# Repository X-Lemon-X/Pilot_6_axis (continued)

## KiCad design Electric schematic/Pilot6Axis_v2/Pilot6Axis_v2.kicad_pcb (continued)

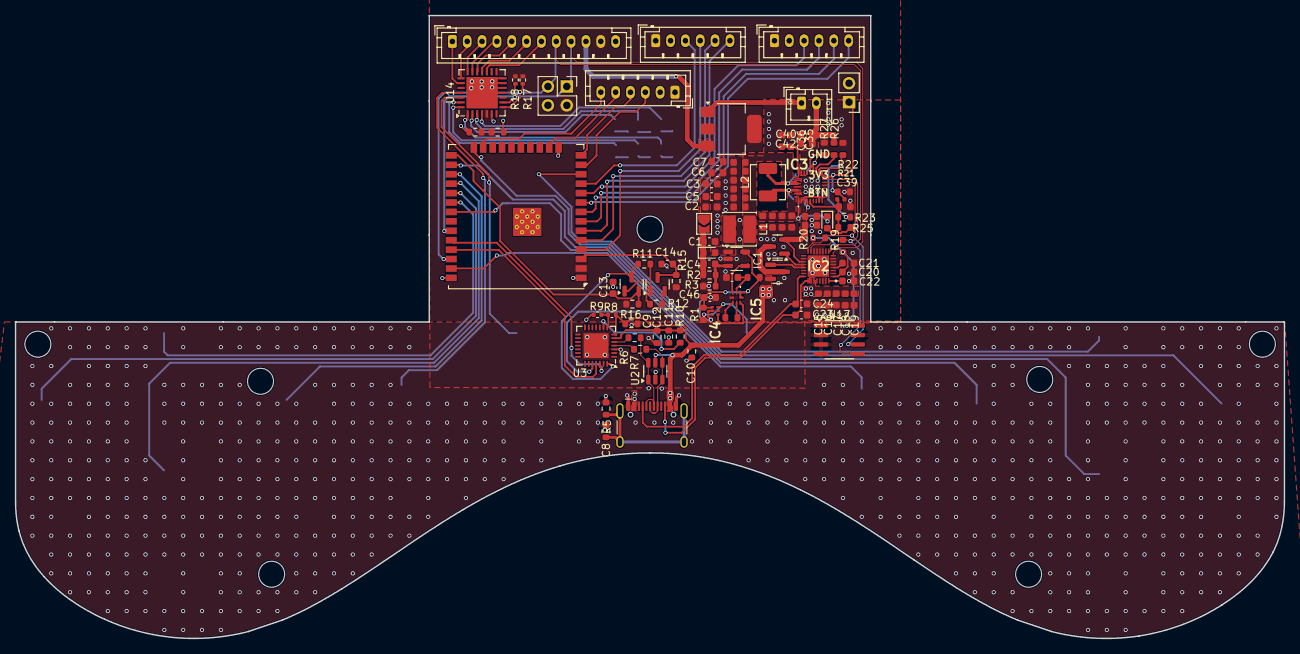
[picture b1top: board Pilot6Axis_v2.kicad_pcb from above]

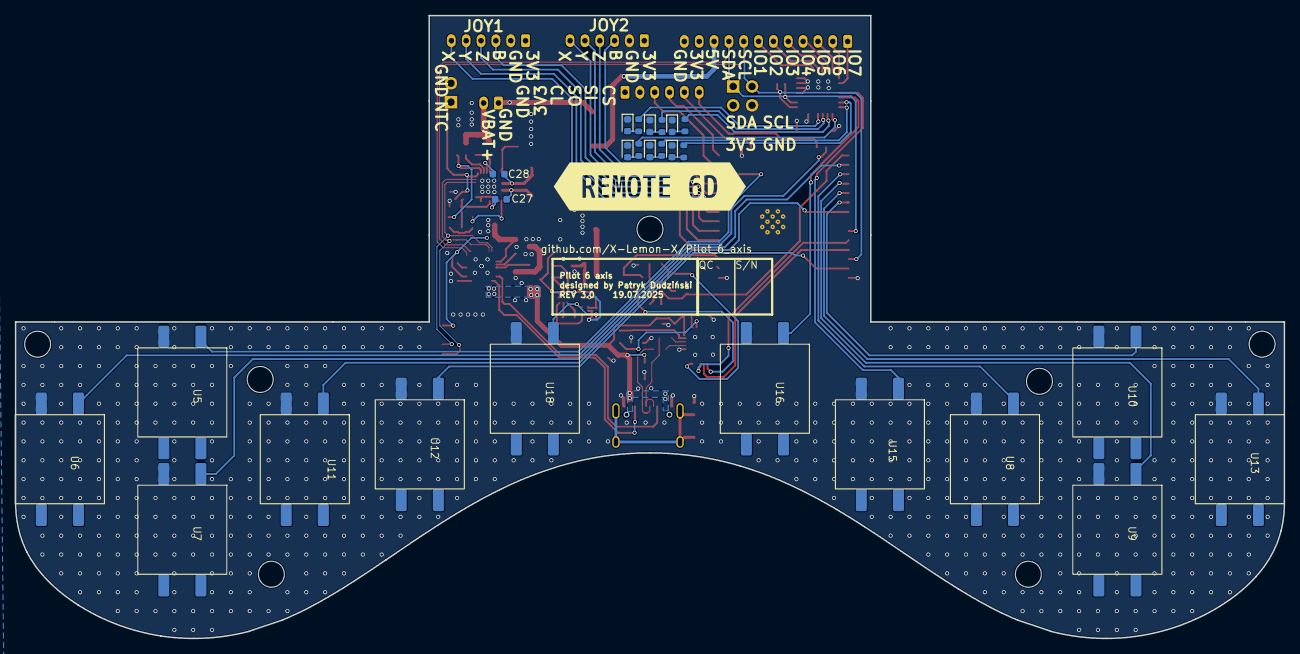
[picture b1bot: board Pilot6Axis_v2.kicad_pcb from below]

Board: 2 copper layers, 171.0 x 83.9 mm, 126 parts (27 on the bottom side), 99 nets.

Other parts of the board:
kibuzzard-6828A41A: G***; kibuzzard-6828A41A

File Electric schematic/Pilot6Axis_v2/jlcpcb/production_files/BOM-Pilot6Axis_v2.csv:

Comment,Designator,Footprint,LCSC,Quantity
10uH,L1,L_Cenker_CKCS4018,C1035,1
40.5k,R2,R_0603_1608Metric,C12447,1
100n,"C10,C11,C17,C18,C19,C22,C25,C26,C3,C34,C43,C45,C46,C7",R_0603_1608Metric,C14663,14
1k,R10,R_0603_1608Metric,C14676,1
1nF,"C13,C14,C35,C36,C47,C5,C6",C_0603_1608Metric,C1588,7
220pF,"C23,C24,C4",C_0603_1608Metric,C1603,3
47nF,"C27,C28",C_0603,C1622,2
4.7uF,"C1,C16,C39",C_0603_1608Metric,C19666,3
10u,"C12,C44,C9",R_0603_1608Metric,C19702,3
S9014,"Q1,Q2",Q_SOT-23,C20069130,2
AO3400A,"Q3,Q4",Q_SOT-23,C20917,2
1kΩ,"R13,R14,R25,R28,R30,R31,R32",R_0603,C21190,7
100Ω,R26,R_0603,C22775,1
Red,"D2,D3,D4,D5,D6,D7,D8",D_0603,C2286,7
30kΩ,R22,R_0603,C22984,1
330Ω,R4,R_0603,C23138,1
4.7kΩ,"R19,R20",R_0603,C23162,2
22Ω,R29,R_0603,C23345,1
100kΩ,"R1,R24",R_0603,C25803,2
5.1kΩ,R21,R_0402,C25905,1
13.3k,"R11,R12,R15,R16,R17,R18,R3,R8,R9",R_0603_1608Metric,C25952,9
USB_C_Receptacle_USB2.0_16P,J3,USB_C_Receptacle_HCTL_HC-TYPE-C-16P-01A,C2765186,1
MBR0520,D1,D_0603_1608Metric,C2858712,1
LM27313XMFX_NOPB,IC1,SOT-23-5,C341750,1
3kΩ,R27,R_0603,C4211,1
33k,R5,R_0603_1608Metric,C4216,1
USBLC6-2SC6,U2,SOT-23-6,C5180249,1
10nF,C8,R_0603_1608Metric,C57112,1
AMS1117-3.3,U1,SOT-223-3_TabPin2,C6186,1
22R,"R6,R7",R_0603_1608Metric,C71618,2
10uF,"C15,C2,C20,C21,C29,C30,C31,C32,C33,C37,C38,C40,C41,C42",C_0603,C96446,14
CP2102N-Axx-xQFN28,U3,QFN-28-1EP_5x5mm_P0.5mm_EP3.35x3.35mm,C964632,1
127k,R23,R_0603_1608Metric,,1
Conn_01x06,J9,JST_PH_B6B-PH-K_1x06_P2.00mm_Vertical,,1
TPS25751SRSMR,IC2,QFN40P400X400X100-33N-D,,1
SolderJumper_2_Bridged,JP1,SolderJumper-2_P1.3mm_Open_TrianglePad1.0x1.5mm,,1
Conn_01x12,J8,JST_PH_B12B-PH-K_1x12_P2.00mm_Vertical,,1
Conn_01x06,J4,JST_PH_B6B-PH-K_1x06_P2.00mm_Vertical,,1
MCP23017_ML,U14,QFN-28-1EP_6x6mm_P0.65mm_EP4.25x4.25mm,,1
10k,TH1,PinHeader_1x02_P2.54mm_Vertical,,1
TPS3422EGDRYR,IC4,DRY_R-PUSON-N6_,,1
SN74LVC1G74RSE2,IC5,SN74LVC1G74RSE2,,1
BQ25792RQMR,IC3,BQ25792RQMR,,1
1u,L2,L_APV_APH0420,,1
ESP32-WROOM-32U,U4,ESP32-WROOM-32U,,1
Battery input,J1,JST_PH_B2B-PH-K_1x02_P2.00mm_Vertical,,1
Conn_01x06,J10,JST_PH_B6B-PH-K_1x06_P2.00mm_Vertical,,1
Oled,J6,PinSocket_2x02_P2.54mm_Vertical,,1
~,U12,ts-1212f,,1
~,U7,ts-1212f,,1
~,U9,ts-1212f,,1
Power switch,U18,ts-1212f,,1
~,U6,ts-1212f,,1
~,U10,ts-1212f,,1
~,U11,ts-1212f,,1
~,U8,ts-1212f,,1
~,U15,ts-1212f,,1
~,U13,ts-1212f,,1
~,U16,ts-1212f,,1
~,U5,ts-1212f,,1
CAT24C512WI-GT3,U17,SOIC-8_3.9x4.9mm_P1.27mm,,1

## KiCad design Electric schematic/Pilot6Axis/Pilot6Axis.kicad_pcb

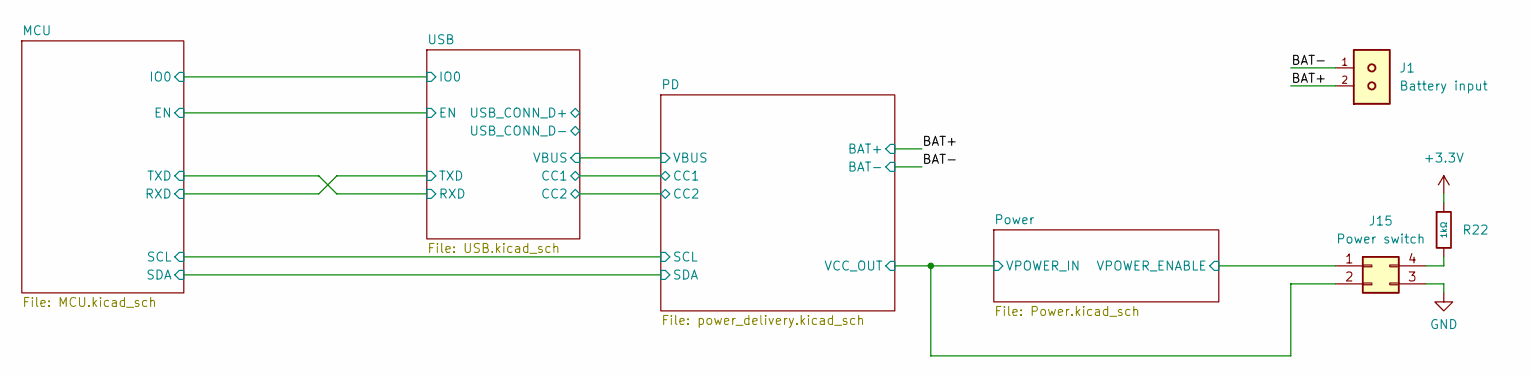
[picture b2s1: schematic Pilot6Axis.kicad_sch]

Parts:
J1: Battery input; Molex_KK-254_AE-6410-02A_1x02_P2.54mm_Vertical
J15: Power switch; Molex_KK-254_AE-6410-04A_1x04_P2.54mm_Vertical
R22: 1kΩ; R_0603; Overload Voltage (Max) 75V; Tolerance ±1%; Part 0603WAF1001T5E; LCSC C21190

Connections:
+3.3V: R22.1; also elsewhere on the board
/BAT+: J1.2; also elsewhere on the board
/PD/VCC_OUT: J15.2; also elsewhere on the board
/Power/VPOWER_ENABLE: J15.1; also elsewhere on the board
GND: J1.1, J15.3; also elsewhere on the board
unnamed: J15.4, R22.2

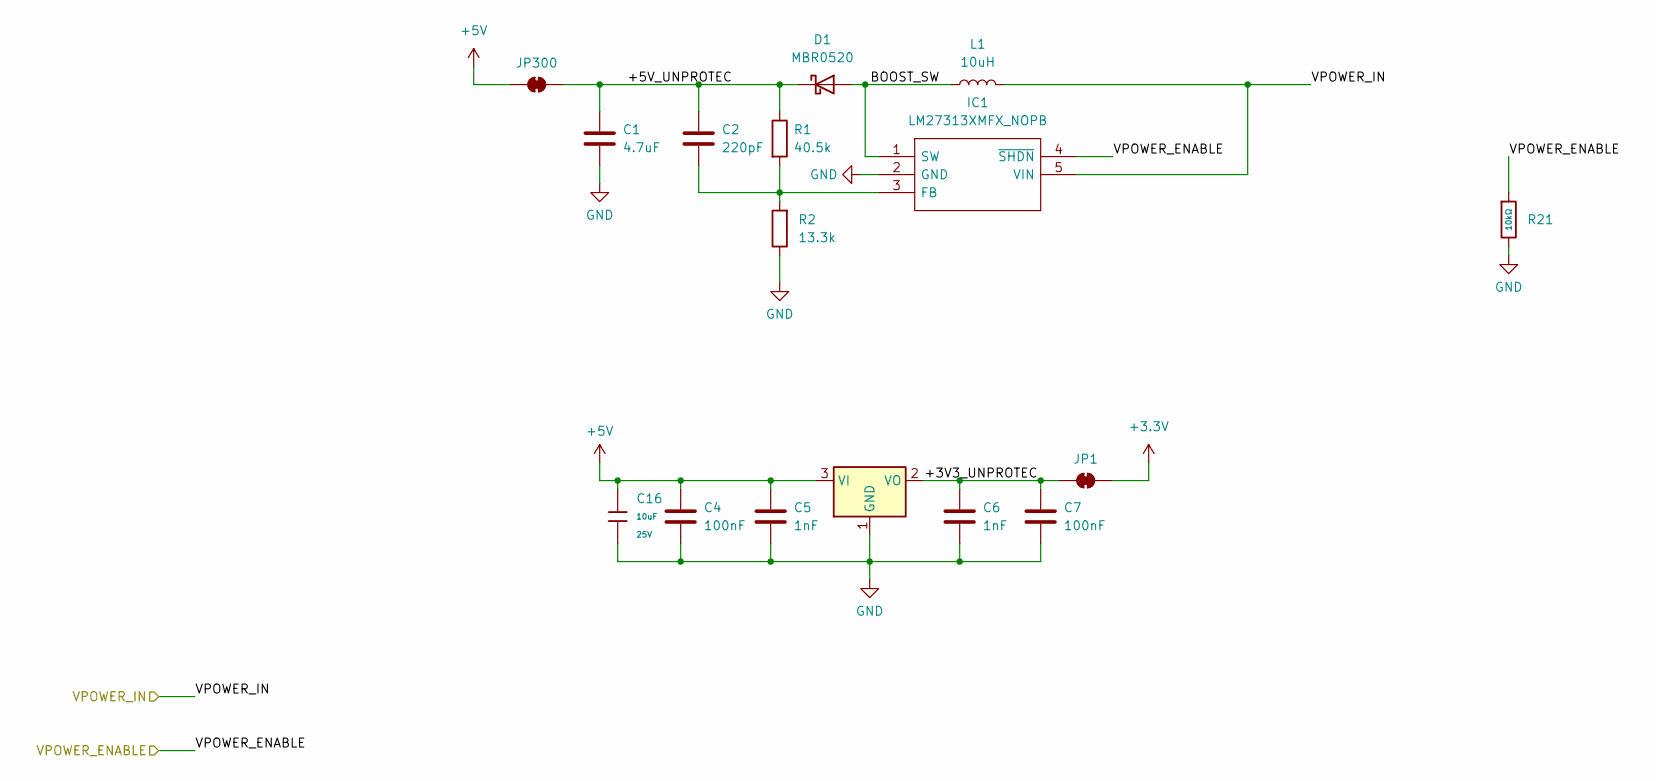
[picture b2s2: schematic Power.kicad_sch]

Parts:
C1: 4.7uF; C_0603_1608Metric; LCSC C19666
C2: 220pF; C_0603_1608Metric; LCSC C1603
C4, C7: 100nF; C_0603_1608Metric; LCSC C14663
C5, C6: 1nF; C_0603_1608Metric; LCSC C1588
C16: 10uF; C_0603; Voltage Rated 25V; Tolerance ±20%; Part CL10A106MA8NRNC; LCSC C96446
D1: MBR0520; D_0603_1608Metric; LCSC C2858712
IC1: LM27313XMFX_NOPB; SOT-23-5; Manufacturer_Part_Number LM27313XMFX/NOPB; Mouser Part Number 926-LM27313XMFX/NOPB
JP1, JP300: SolderJumper_2_Bridged; SolderJumper-2_P1.3mm_Open_TrianglePad1.0x1.5mm
L1: 10uH; L_Cenker_CKCS4018; LCSC C1035
R1: 40.5k; R_0603_1608Metric; LCSC C12447
R2: 13.3k; R_0603_1608Metric; LCSC C25952
R21: 10kΩ; R_0603; Overload Voltage (Max) 75V; Tolerance ±1%; Part 0603WAF1002T5E; LCSC C25804
U1: AMS1117-3.3; SOT-223-3_TabPin2; LCSC C6186

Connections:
+3.3V: JP1.2 (B); also elsewhere on the board
+5V: C4.1, C5.1, C16.1, JP300.1 (A), U1.3 (VI); also elsewhere on the board
/PD/VCC_OUT: IC1.5 (VIN), L1.2; also elsewhere on the board
/Power/+3V3_UNPROTEC: C6.1, C7.1, JP1.1 (A), U1.2 (VO)
/Power/+5V_UNPROTEC: C1.1, C2.2, D1.1 (K), JP300.2 (B), R1.1
/Power/BOOST_SW: D1.2 (A), IC1.1 (SW), L1.1
/Power/VPOWER_ENABLE: IC1.4 (~SHDN), R21.1; also elsewhere on the board
GND: C1.2, C4.2, C5.2, C6.2, C7.2, C16.2, IC1.2 (GND), R2.1, R21.2, U1.1 (GND); also elsewhere on the board
unnamed: C2.1, IC1.3 (FB), R1.2, R2.2

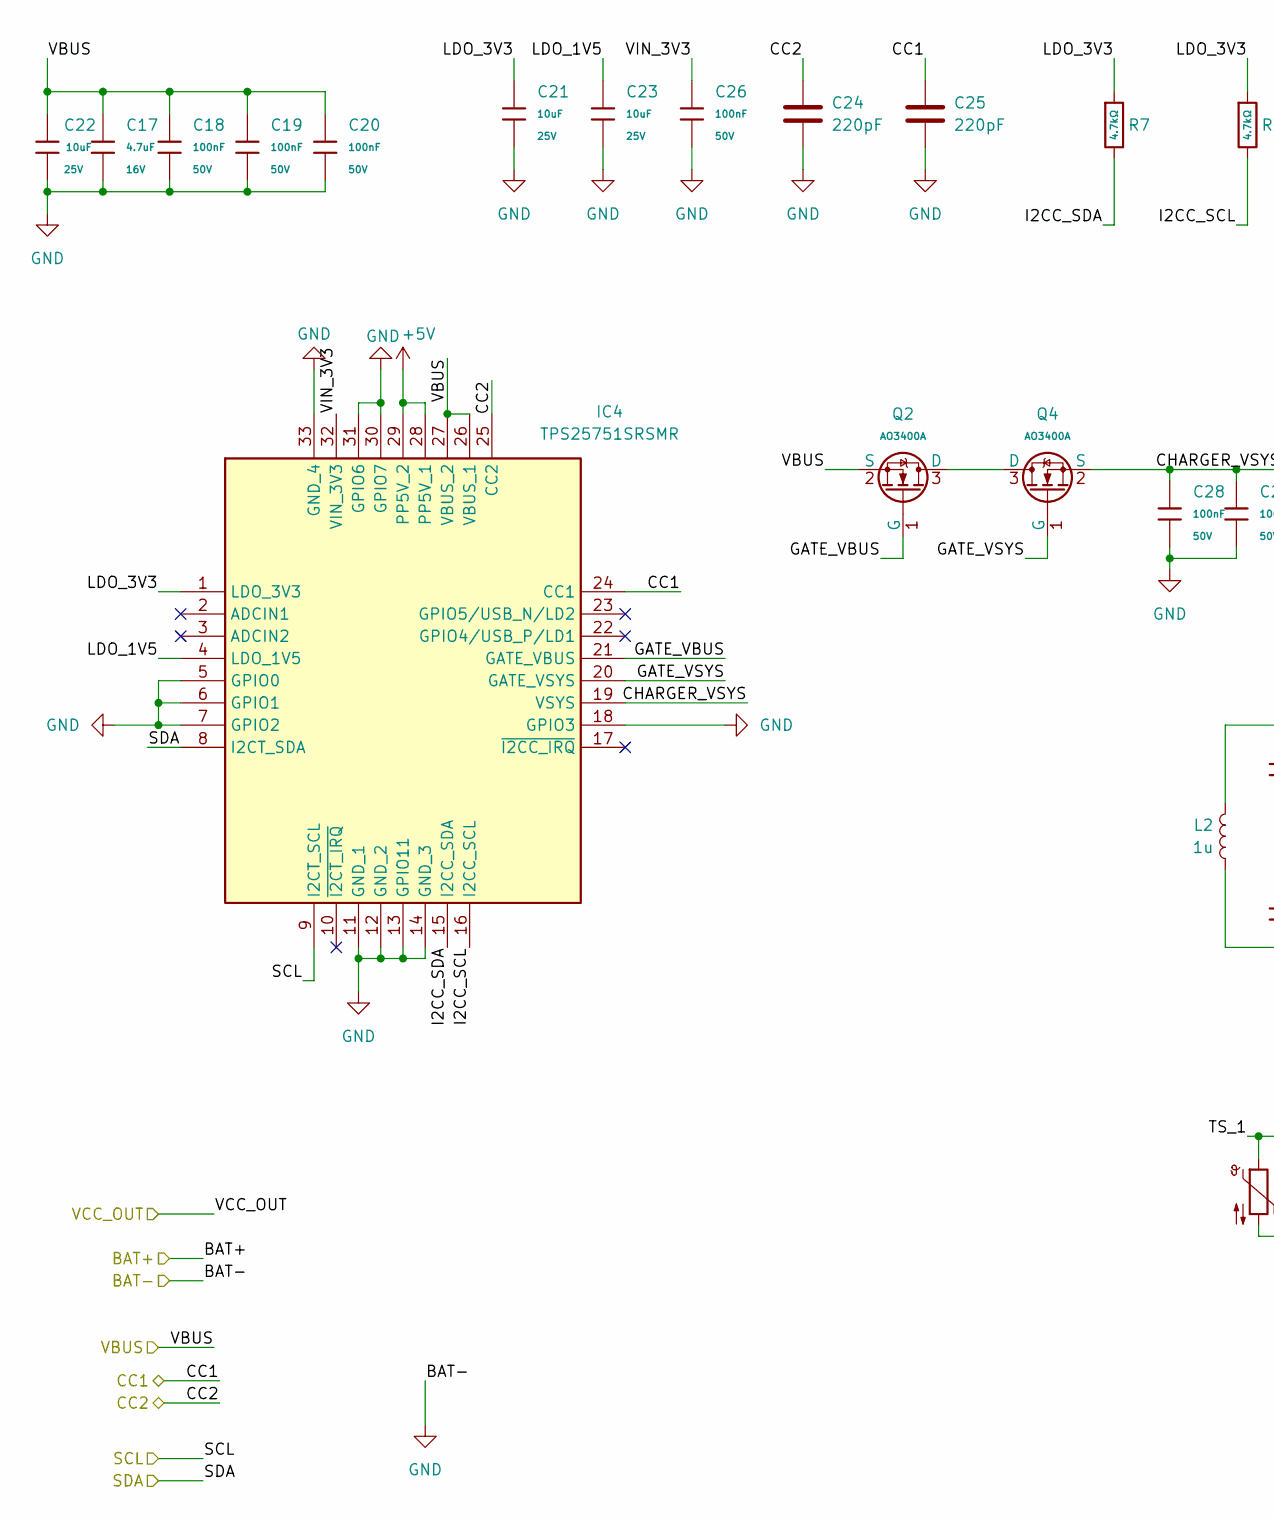
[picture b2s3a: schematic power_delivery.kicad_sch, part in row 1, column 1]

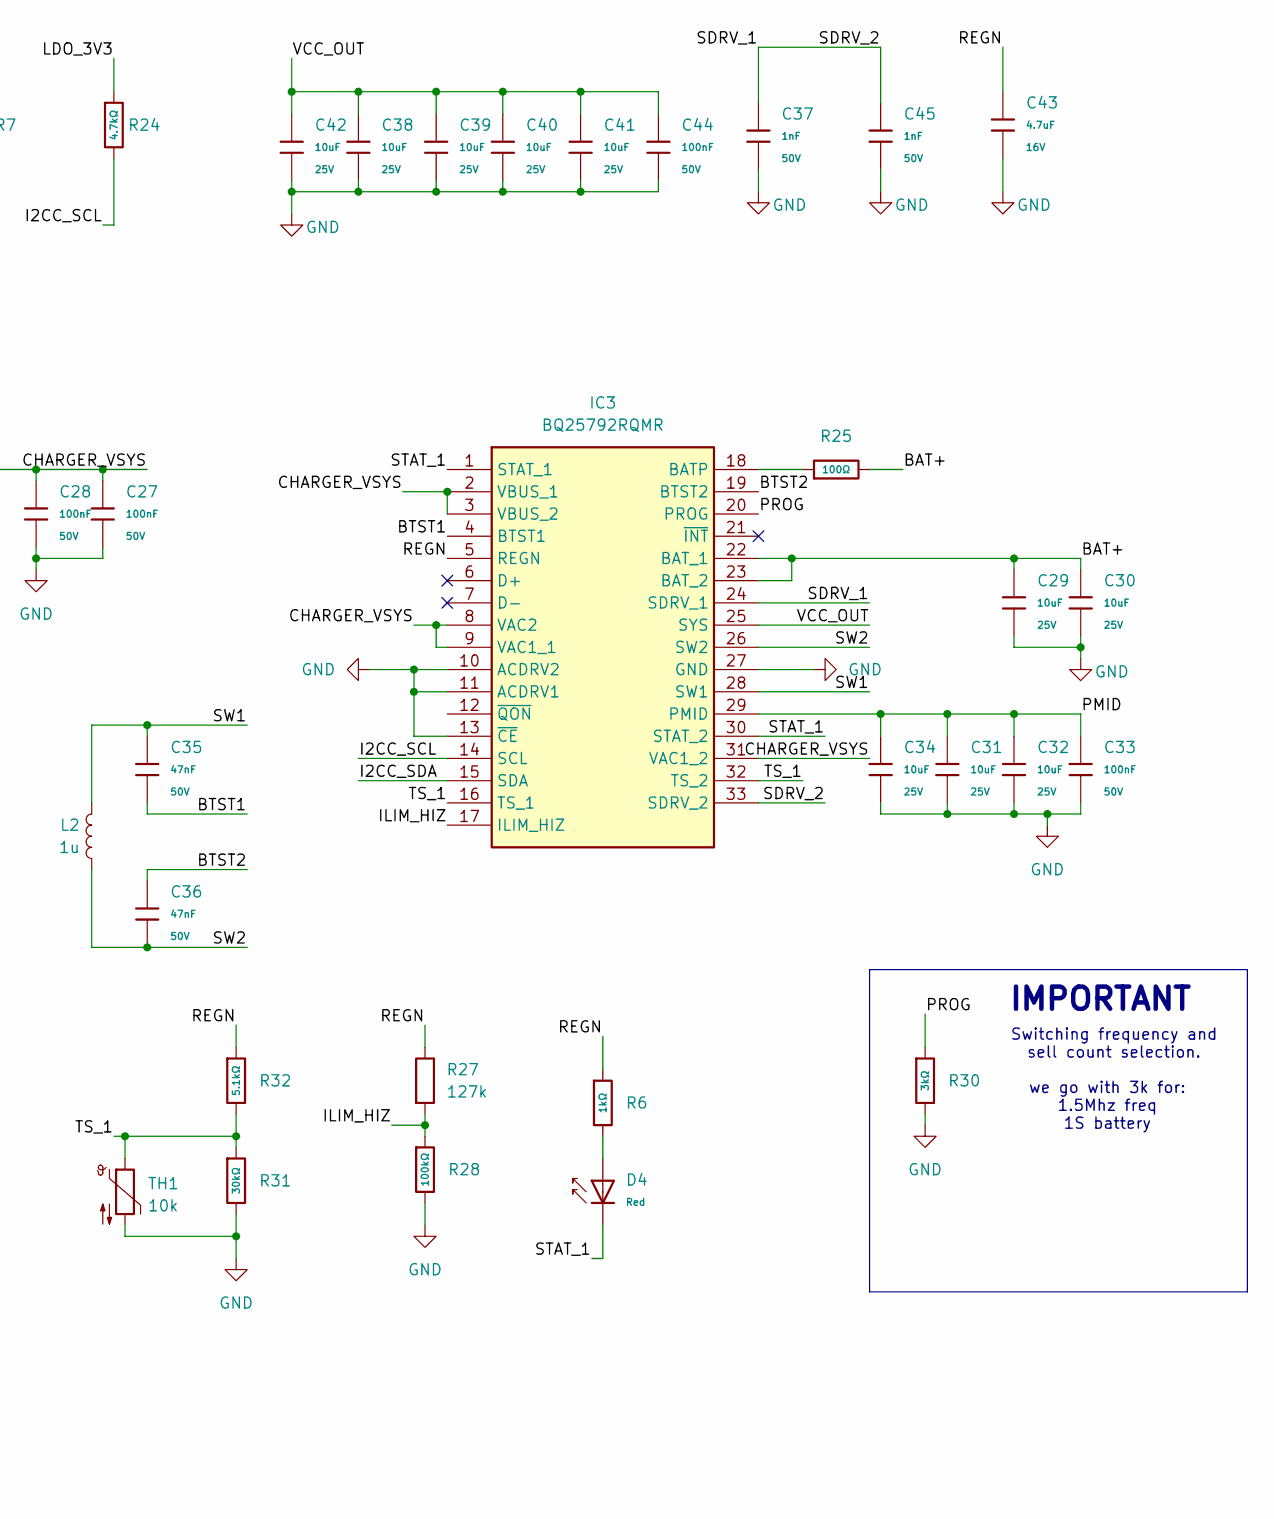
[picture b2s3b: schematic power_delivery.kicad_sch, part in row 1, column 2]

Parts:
C17, C43: 4.7uF; C_0603; Voltage Rated 16V; Tolerance ±10%; Part CL10A475KO8NNNC; LCSC C19666
C18, C19, C20, C26, C27, C28, C33, C44: 100nF; C_0603; Voltage Rated 50V; Tolerance ±10%; Part CC0603KRX7R9BB104; LCSC C14663
C21, C22, C23, C29, C30, C31, C32, C34, C38, C39, C40, C41, C42: 10uF; C_0603; Voltage Rated 25V; Tolerance ±20%; Part CL10A106MA8NRNC; LCSC C96446
C24, C25: 220pF; C_0603_1608Metric; LCSC C1603
C35, C36: 47nF; C_0603; Voltage Rated 50V; Tolerance ±10%; Part CL10B473KB8NNNC; LCSC C1622
C37, C45: 1nF; C_0603; Voltage Rated 50V; Tolerance ±10%; Part CL10B102KB8NNNC; LCSC C1588
D4: Red; D_0603; Part KT-0603R; LCSC C2286
IC3: BQ25792RQMR; Manufacturer_Part_Number BQ25792RQMR; Mouser Part Number 595-BQ25792RQMR
IC4: TPS25751SRSMR; QFN40P400X400X100-33N-D; Manufacturer_Part_Number TPS25751SRSMR; Mouser Part Number 595-TPS25751SRSMR
L2: 1u; L_APV_APH0420
Q2, Q4: AO3400A; Q_SOT-23; Part AO3400A; LCSC C20917
R6: 1kΩ; R_0603; Overload Voltage (Max) 75V; Tolerance ±1%; Part 0603WAF1001T5E; LCSC C21190
R7, R24: 4.7kΩ; R_0603; Overload Voltage (Max) 75V; Tolerance ±1%; Part 0603WAF4701T5E; LCSC C23162
R25: 100Ω; R_0603; Overload Voltage (Max) 75V; Tolerance ±1%; Part 0603WAF1000T5E; LCSC C22775
R27: 127k; R_0603_1608Metric
R28: 100kΩ; R_0603; Overload Voltage (Max) 75V; Tolerance ±1%; Part 0603WAF1003T5E; LCSC C25803
R30: 3kΩ; R_0603; Overload Voltage (Max) 75V; Tolerance ±1%; Part 0603WAF3001T5E; LCSC C4211
R31: 30kΩ; R_0603; Overload Voltage (Max) 75V; Tolerance ±1%; Part 0603WAF3002T5E; LCSC C22984
R32: 5.1kΩ; R_0402; Overload Voltage (Max) 50V; Tolerance ±1%; Part 0402WGF5101TCE; LCSC C25905
TH1: 10k; PinHeader_1x02_P2.54mm_Vertical

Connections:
+5V: IC4.28 (PP5V_1), IC4.29 (PP5V_2); also elsewhere on the board
/BAT+: C29.1, C30.1, IC3.22 (BAT_1), IC3.23 (BAT_2), R25.2; also elsewhere on the board
/MCU/SCL: IC4.9 (I2CT_SCL); also elsewhere on the board
/MCU/SDA: IC4.8 (I2CT_SDA); also elsewhere on the board
/PD/BTST1: C35.2, IC3.4 (BTST1)
/PD/BTST2: C36.1, IC3.19 (BTST2)
/PD/CC1: C25.2, IC4.24 (CC1); also elsewhere on the board
/PD/CC2: C24.2, IC4.25 (CC2); also elsewhere on the board
/PD/CHARGER_VSYS: C27.1, C28.1, IC3.2 (VBUS_1), IC3.3 (VBUS_2), IC3.8 (VAC2), IC3.9 (VAC1_1), IC3.31 (VAC1_2), IC4.19 (VSYS), Q4.2 (S)
/PD/GATE_VBUS: IC4.21 (GATE_VBUS), Q2.1 (G)
/PD/GATE_VSYS: IC4.20 (GATE_VSYS), Q4.1 (G)
/PD/I2CC_SCL: IC3.14 (SCL), IC4.16 (I2CC_SCL), R24.2
/PD/I2CC_SDA: IC3.15 (SDA), IC4.15 (I2CC_SDA), R7.2
/PD/ILIM_HIZ: IC3.17 (ILIM_HIZ), R27.2, R28.1
/PD/LDO_1V5: C23.1, IC4.4 (LDO_1V5)
/PD/LDO_3V3: C21.1, IC4.1 (LDO_3V3), R7.1, R24.1
/PD/PMID: C31.1, C32.1, C33.1, C34.1, IC3.29 (PMID)
/PD/PROG: IC3.20 (PROG), R30.1
/PD/REGN: C43.1, IC3.5 (REGN), R6.1, R27.1, R32.1
/PD/SDRV_1: C37.1, C45.1, IC3.24 (SDRV_1), IC3.33 (SDRV_2)
/PD/STAT_1: D4.1, IC3.1 (STAT_1), IC3.30 (STAT_2)
/PD/SW1: C35.1, IC3.28 (SW1), L2.1
/PD/SW2: C36.2, IC3.26 (SW2), L2.2
/PD/TS_1: IC3.16 (TS_1), IC3.32 (TS_2), R31.1, R32.2, TH1.1
/PD/VBUS: C17.1, C18.1, C19.1, C20.1, C22.1, IC4.26 (VBUS_1), IC4.27 (VBUS_2), Q2.2 (S); also elsewhere on the board
/PD/VCC_OUT: C38.1, C39.1, C40.1, C41.1, C42.1, C44.1, IC3.25 (SYS); also elsewhere on the board
/PD/VIN_3V3: C26.1, IC4.32 (VIN_3V3)
GND: C17.2, C18.2, C19.2, C20.2, C21.2, C22.2, C23.2, C24.1, C25.1, C26.2, C27.2, C28.2, C29.2, C30.2, C31.2, C32.2, C33.2, C34.2, C37.2, C38.2, C39.2, C40.2, C41.2, C42.2, C43.2, C44.2, C45.2, IC3.10 (ACDRV2), IC3.11 (ACDRV1), IC3.13 (~CE), IC3.27 (GND), IC4.5 (GPIO0), IC4.6 (GPIO1), IC4.7 (GPIO2), IC4.11 (GND_1), IC4.12 (GND_2), IC4.13 (GPIO11), IC4.14 (GND_3), IC4.18 (GPIO3), IC4.30 (GPIO7), IC4.31 (GPIO6), IC4.33 (GND_4), R28.2, R30.2, R31.2, TH1.2; also elsewhere on the board
unnamed: D4.2, R6.2
unnamed: IC3.18 (BATP), R25.1
unnamed: Q2.3 (D), Q4.3 (D)

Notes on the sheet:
Switching frequency and sell count selection.
we go with 3k for: 1.5Mhz freq 1S battery
IMPORTANT

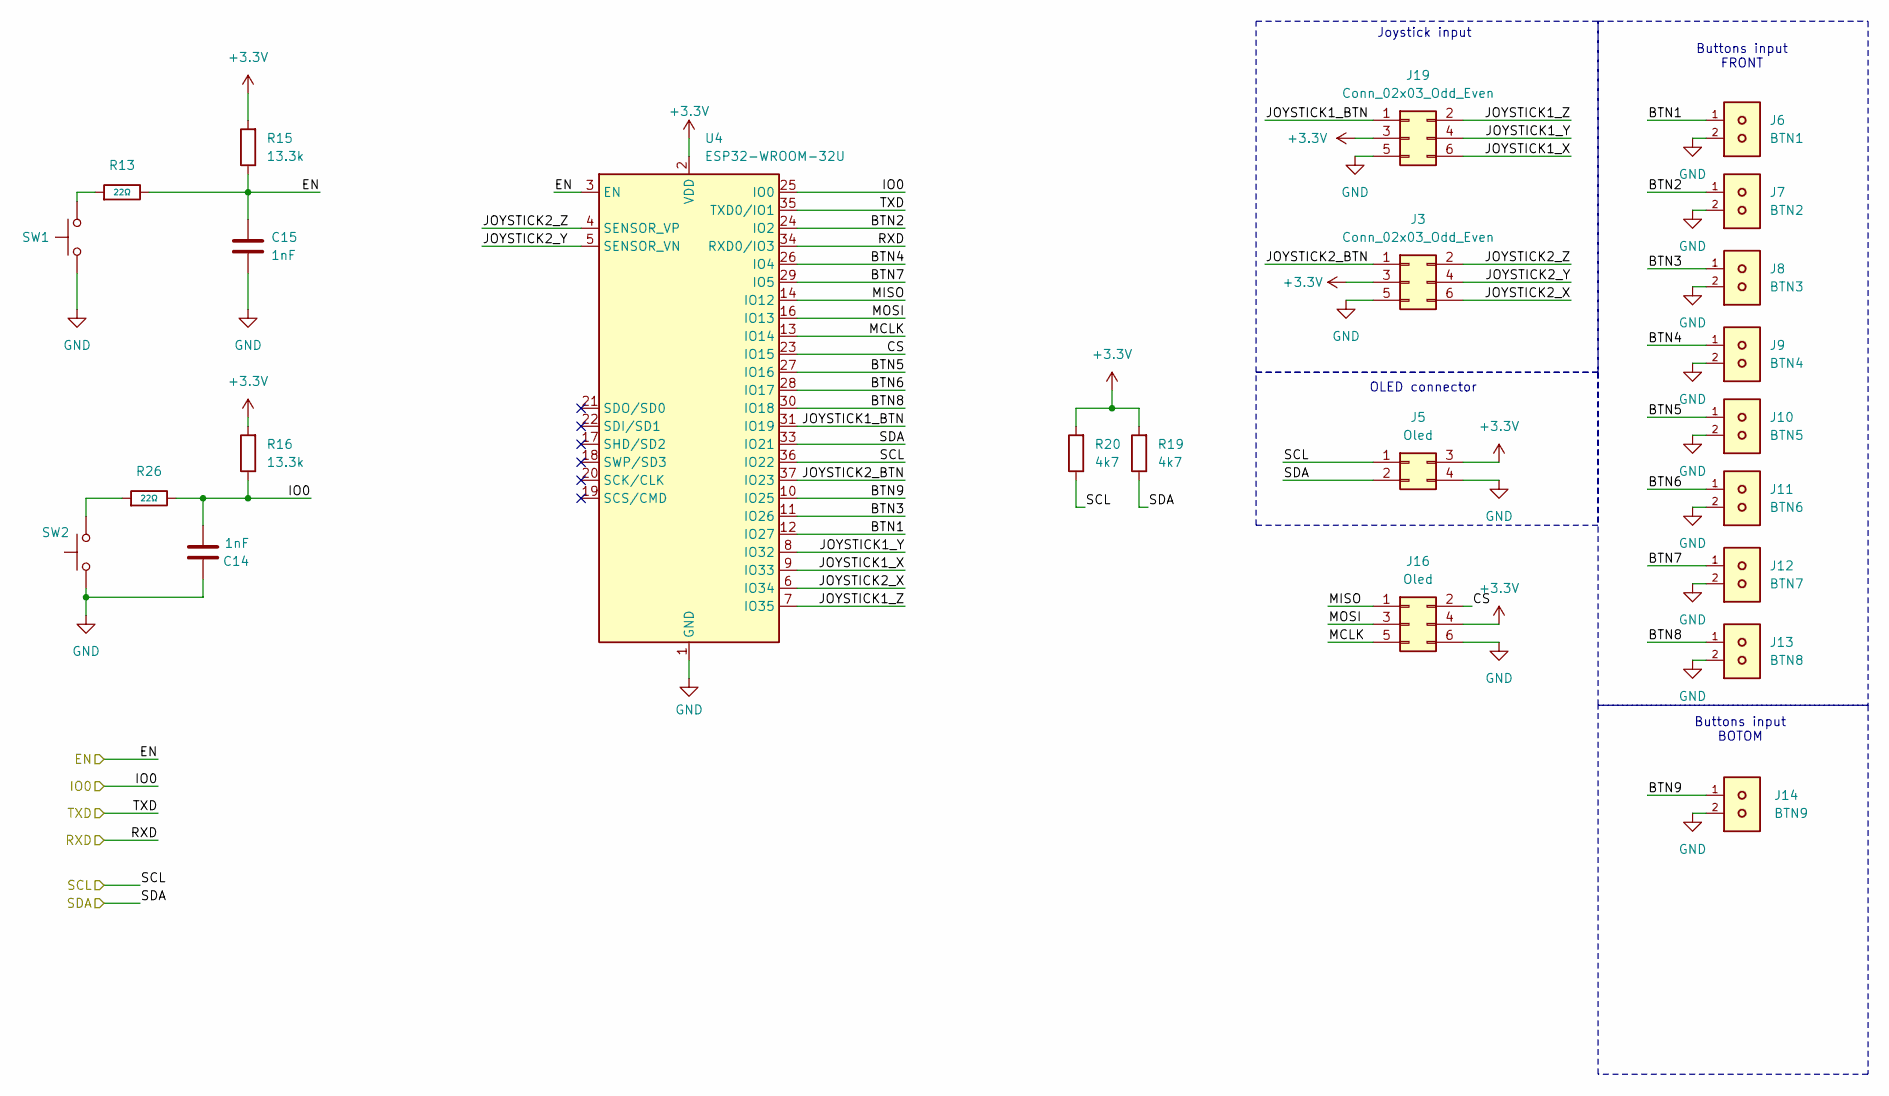
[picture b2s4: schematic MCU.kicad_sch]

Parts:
C14, C15: 1nF; C_0603_1608Metric; LCSC C1588
J3, J19: Conn_02x03_Odd_Even; PinSocket_2x03_P2.54mm_Vertical
J5: Oled; PinSocket_2x02_P2.54mm_Vertical
J6: BTN1; Molex_KK-254_AE-6410-02A_1x02_P2.54mm_Vertical
J7: BTN2; Molex_KK-254_AE-6410-02A_1x02_P2.54mm_Vertical
J8: BTN3; Molex_KK-254_AE-6410-02A_1x02_P2.54mm_Vertical
J9: BTN4; Molex_KK-254_AE-6410-02A_1x02_P2.54mm_Vertical
J10: BTN5; Molex_KK-254_AE-6410-02A_1x02_P2.54mm_Vertical
J11: BTN6; Molex_KK-254_AE-6410-02A_1x02_P2.54mm_Vertical
J12: BTN7; Molex_KK-254_AE-6410-02A_1x02_P2.54mm_Vertical
J13: BTN8; Molex_KK-254_AE-6410-02A_1x02_P2.54mm_Vertical
J14: BTN9; Molex_KK-254_AE-6410-02A_1x02_P2.54mm_Vertical
J16: Oled; PinSocket_2x03_P2.54mm_Vertical
R13, R26: 22Ω; R_0603; Overload Voltage (Max) 75V; Tolerance ±1%; Part 0603WAF220JT5E; LCSC C23345
R15, R16: 13.3k; R_0603_1608Metric; LCSC C25952
R19, R20: 4k7; R_0402_1005Metric; LCSC C25952
SW1, SW2: SW_Push; TS1088R02026; LCSC C455280
U4: ESP32-WROOM-32U

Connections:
+3.3V: J3.3, J5.3, J16.4, J19.3, R15.2, R16.2, R19.2, R20.2, U4.2 (VDD); also elsewhere on the board
/MCU/BTN1: J6.1, U4.12 (IO27)
/MCU/BTN2: J7.1, U4.24 (IO2)
/MCU/BTN3: J8.1, U4.11 (IO26)
/MCU/BTN4: J9.1, U4.26 (IO4)
/MCU/BTN5: J10.1, U4.27 (IO16)
/MCU/BTN6: J11.1, U4.28 (IO17)
/MCU/BTN7: J12.1, U4.29 (IO5)
/MCU/BTN8: J13.1, U4.30 (IO18)
/MCU/BTN9: J14.1, U4.10 (IO25)
/MCU/CS: J16.2, U4.23 (IO15)
/MCU/EN: C15.1, R13.2, R15.1, U4.3 (EN); also elsewhere on the board
/MCU/IO0: C14.2, R16.1, R26.2, U4.25 (IO0); also elsewhere on the board
/MCU/JOYSTICK1_BTN: J19.1, U4.31 (IO19)
/MCU/JOYSTICK1_X: J19.6, U4.9 (IO33)
/MCU/JOYSTICK1_Y: J19.4, U4.8 (IO32)
/MCU/JOYSTICK1_Z: J19.2, U4.7 (IO35)
/MCU/JOYSTICK2_BTN: J3.1, U4.37 (IO23)
/MCU/JOYSTICK2_X: J3.6, U4.6 (IO34)
/MCU/JOYSTICK2_Y: J3.4, U4.5 (SENSOR_VN)
/MCU/JOYSTICK2_Z: J3.2, U4.4 (SENSOR_VP)
/MCU/MCLK: J16.5, U4.13 (IO14)
/MCU/MISO: J16.1, U4.14 (IO12)
/MCU/MOSI: J16.3, U4.16 (IO13)
/MCU/RXD: U4.34 (RXD0/IO3); also elsewhere on the board
/MCU/SCL: J5.1, R20.1, U4.36 (IO22); also elsewhere on the board
/MCU/SDA: J5.2, R19.1, U4.33 (IO21); also elsewhere on the board
/MCU/TXD: U4.35 (TXD0/IO1); also elsewhere on the board
GND: C14.1, C15.2, J3.5, J5.4, J6.2, J7.2, J8.2, J9.2, J10.2, J11.2, J12.2, J13.2, J14.2, J16.6, J19.5, SW1.1, SW2.1, U4.1 (GND), U4.15 (GND), U4.38 (GND), U4.39 (GND); also elsewhere on the board
unnamed: R13.1, SW1.2
unnamed: R26.1, SW2.2

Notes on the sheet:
Buttons input BOTOM
Buttons input FRONT
Joystick input
OLED connector

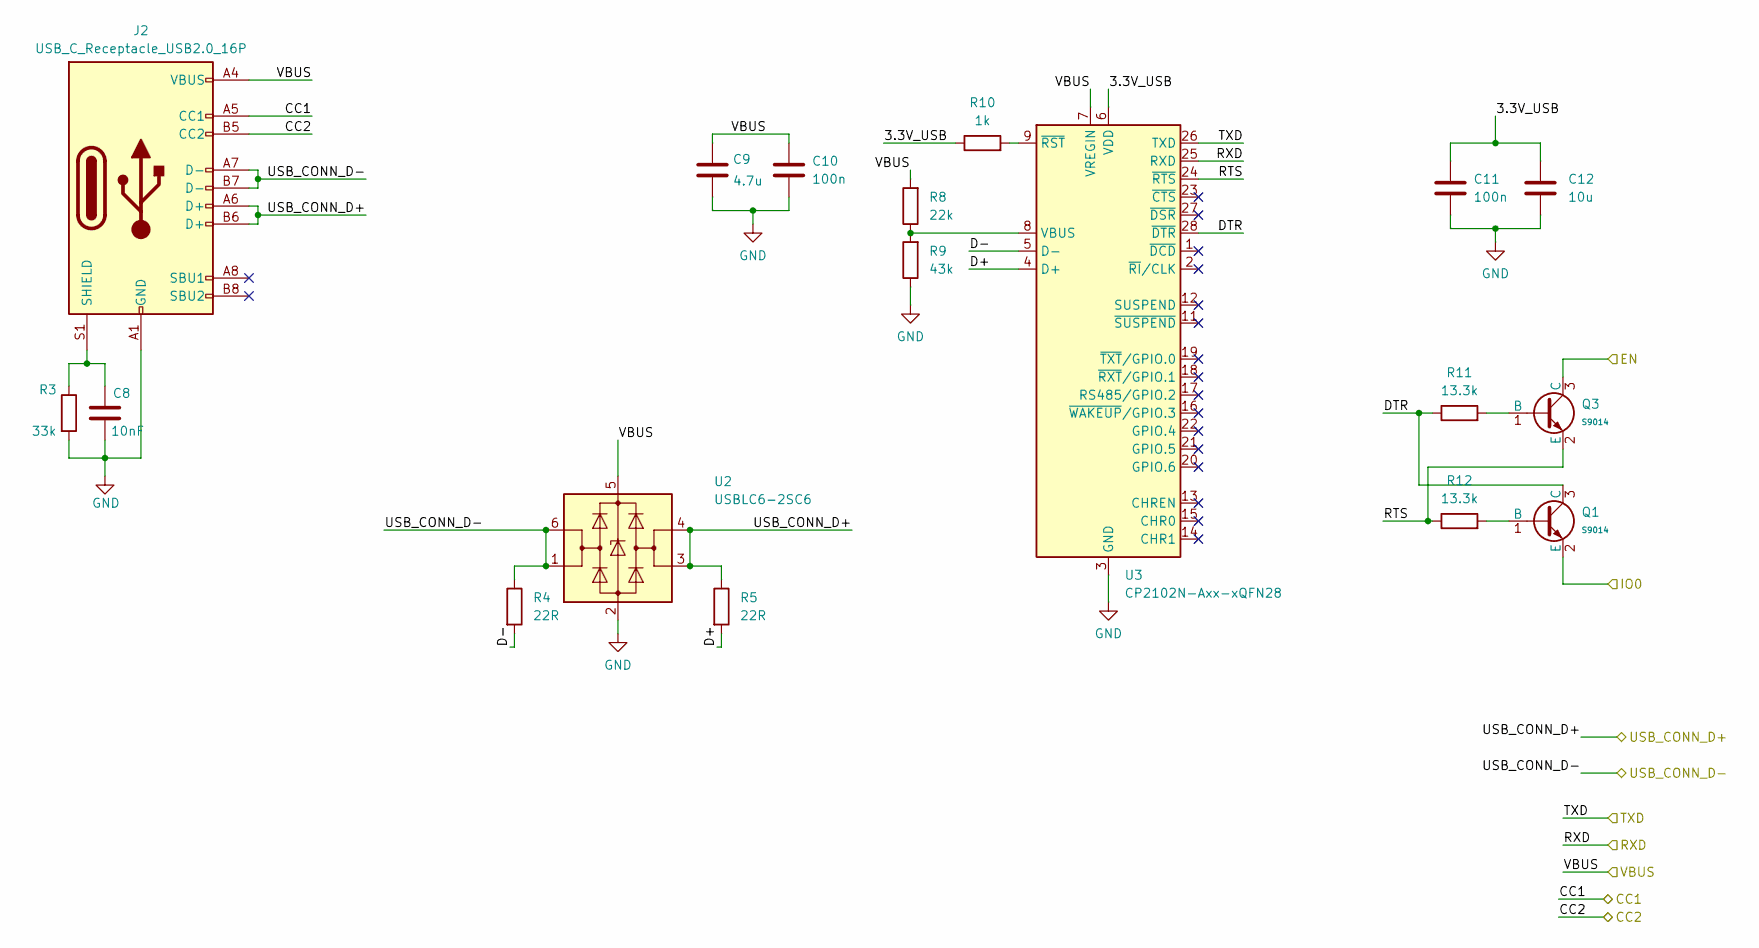
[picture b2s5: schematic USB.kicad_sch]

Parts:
C8: 10nF; R_0603_1608Metric; LCSC C57112
C9: 4.7u; R_0603_1608Metric; LCSC C19702
C10, C11: 100n; R_0603_1608Metric; LCSC C14663
C12: 10u; R_0603_1608Metric; LCSC C19702
J2: USB_C_Receptacle_USB2.0_16P; USB_C_Receptacle_HCTL_HC-TYPE-C-16P-01A; LCSC C2765186
Q1, Q3: S9014; Q_SOT-23; Part S9014; LCSC C20069130
R3: 33k; R_0603_1608Metric; LCSC C4216
R4, R5: 22R; R_0603_1608Metric; LCSC C71618
R8: 22k; R_0402_1005Metric; LCSC C25952
R9: 43k; R_0402_1005Metric; LCSC C25952
R10: 1k; R_0603_1608Metric; LCSC C14676
R11, R12: 13.3k; R_0603_1608Metric; LCSC C25952
U2: USBLC6-2SC6; SOT-23-6; LCSC C5180249
U3: CP2102N-Axx-xQFN28; QFN-28-1EP_5x5mm_P0.5mm_EP3.35x3.35mm; LCSC C964632

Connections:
/MCU/EN: Q3.3 (C); also elsewhere on the board
/MCU/IO0: Q1.2 (E); also elsewhere on the board
/MCU/RXD: U3.26 (TXD); also elsewhere on the board
/MCU/TXD: U3.25 (RXD); also elsewhere on the board
/PD/CC1: J2.A5 (CC1); also elsewhere on the board
/PD/CC2: J2.B5 (CC2); also elsewhere on the board
/PD/VBUS: C9.1, C10.1, J2.A4 (VBUS), J2.A9 (VBUS), J2.B4 (VBUS), J2.B9 (VBUS), R8.2, U2.5 (VBUS), U3.7 (VREGIN); also elsewhere on the board
/USB/3.3V_USB: C11.1, C12.1, R10.1, U3.6 (VDD)
/USB/D+: R5.2, U3.4 (D+)
/USB/D-: R4.2, U3.5 (D-)
/USB/DTR: Q1.3 (C), R11.1, U3.28 (~DTR)
/USB/RTS: Q3.2 (E), R12.1, U3.24 (~RTS)
/USB/USB_CONN_D+: J2.A6 (D+), J2.B6 (D+), R5.1, U2.3 (I/O2), U2.4 (I/O2)
/USB/USB_CONN_D-: J2.A7 (D-), J2.B7 (D-), R4.1, U2.1 (I/O1), U2.6 (I/O1)
GND: C8.2, C9.2, C10.2, C11.2, C12.2, J2.A1 (GND), J2.A12 (GND), J2.B1 (GND), J2.B12 (GND), R3.2, R9.1, U2.2 (GND), U3.3 (GND), U3.29 (GND); also elsewhere on the board
unnamed: C8.1, J2.S1 (SHIELD), R3.1
unnamed: Q1.1 (B), R12.2
unnamed: Q3.1 (B), R11.2
unnamed: R8.1, R9.2, U3.8 (VBUS)
unnamed: R10.2, U3.9 (~RST)
